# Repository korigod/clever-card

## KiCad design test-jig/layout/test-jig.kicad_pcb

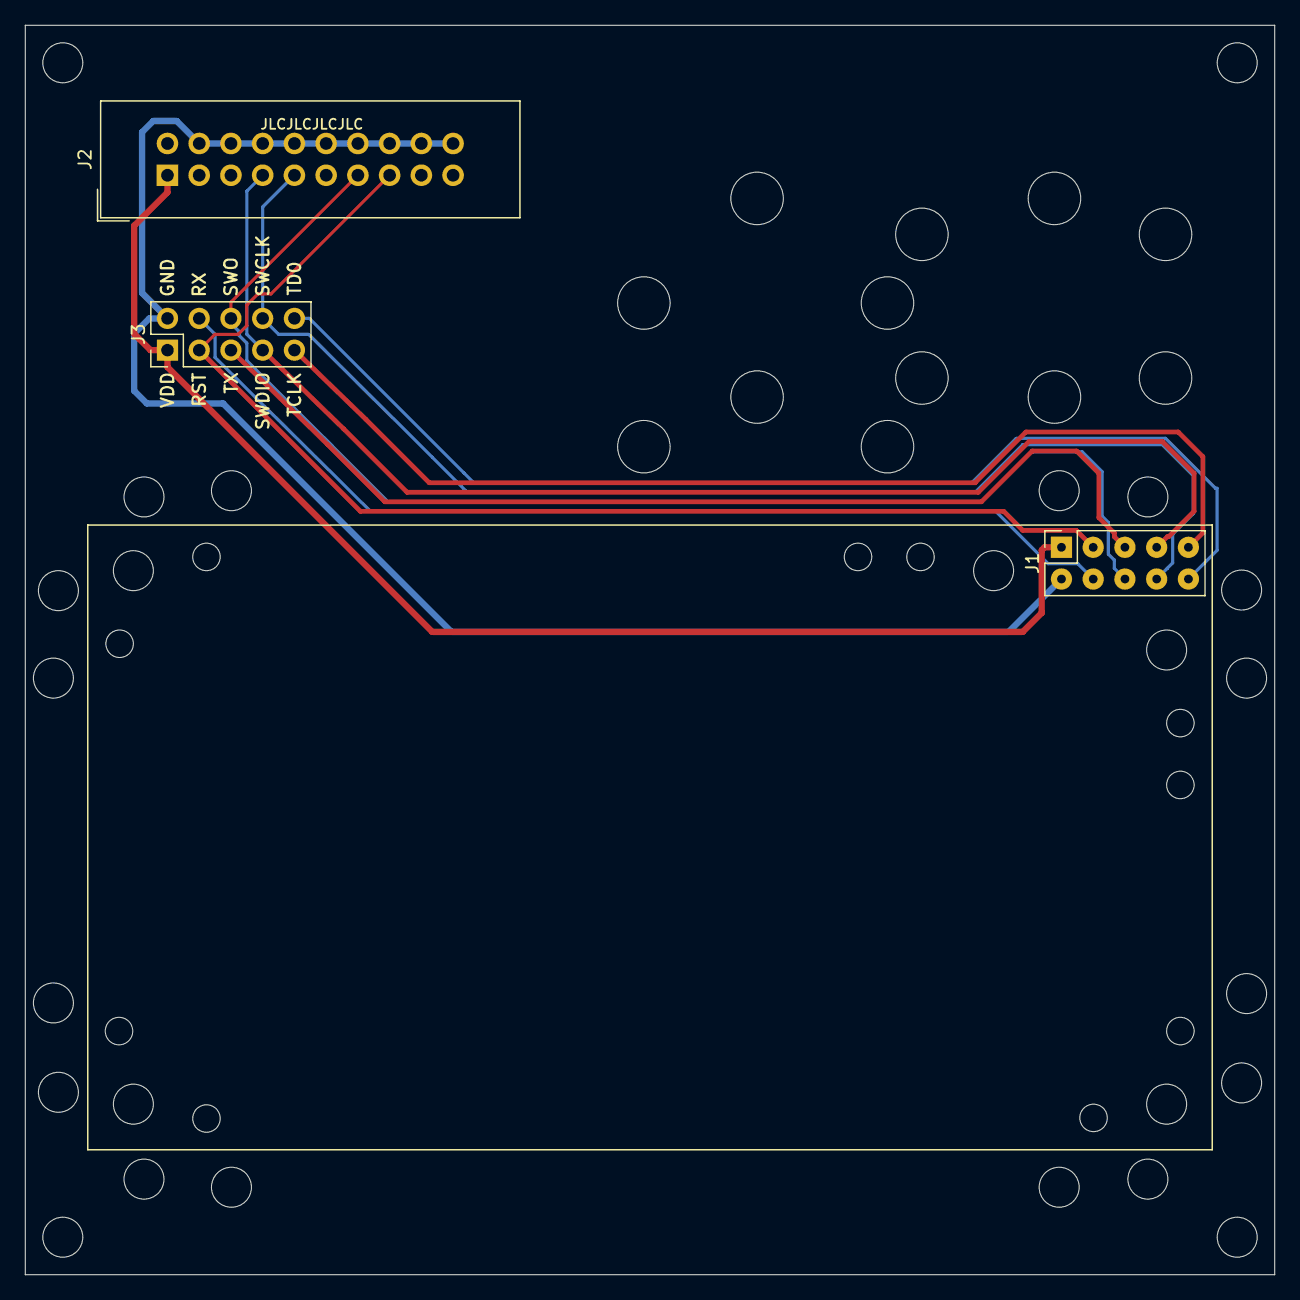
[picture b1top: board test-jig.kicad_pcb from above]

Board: 2 copper layers, 100.0 x 100.0 mm, 3 parts (0 on the bottom side), 10 nets.

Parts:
J1: Conn_02x05_Odd_Even; PinHeader_2x05_P2.54mm_D0.7mm_Vertical
J2: Conn_02x10_Odd_Even; IDC-Header_2x10_P2.54mm_Vertical
J3: Conn_02x05_Odd_Even; PinHeader_2x05_P2.54mm_Vertical

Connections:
DBG_SWCLK: J1.8, J2.9, J3.8
DBG_SWDIO: J1.7, J2.7, J3.7
DBG_SWO: J1.6, J2.13, J3.6
ETM_TCLK: J1.9, J3.9
ETM_TD0: J1.10, J3.10
GND: J1.2, J2.4, J2.6, J2.8, J2.10, J2.12, J2.14, J2.16, J2.18, J2.20, J3.2
RESET: J1.3, J2.15, J3.3
USART_RX: J1.4, J3.4
USART_TX: J1.5, J3.5
VDD: J1.1, J2.1, J3.1

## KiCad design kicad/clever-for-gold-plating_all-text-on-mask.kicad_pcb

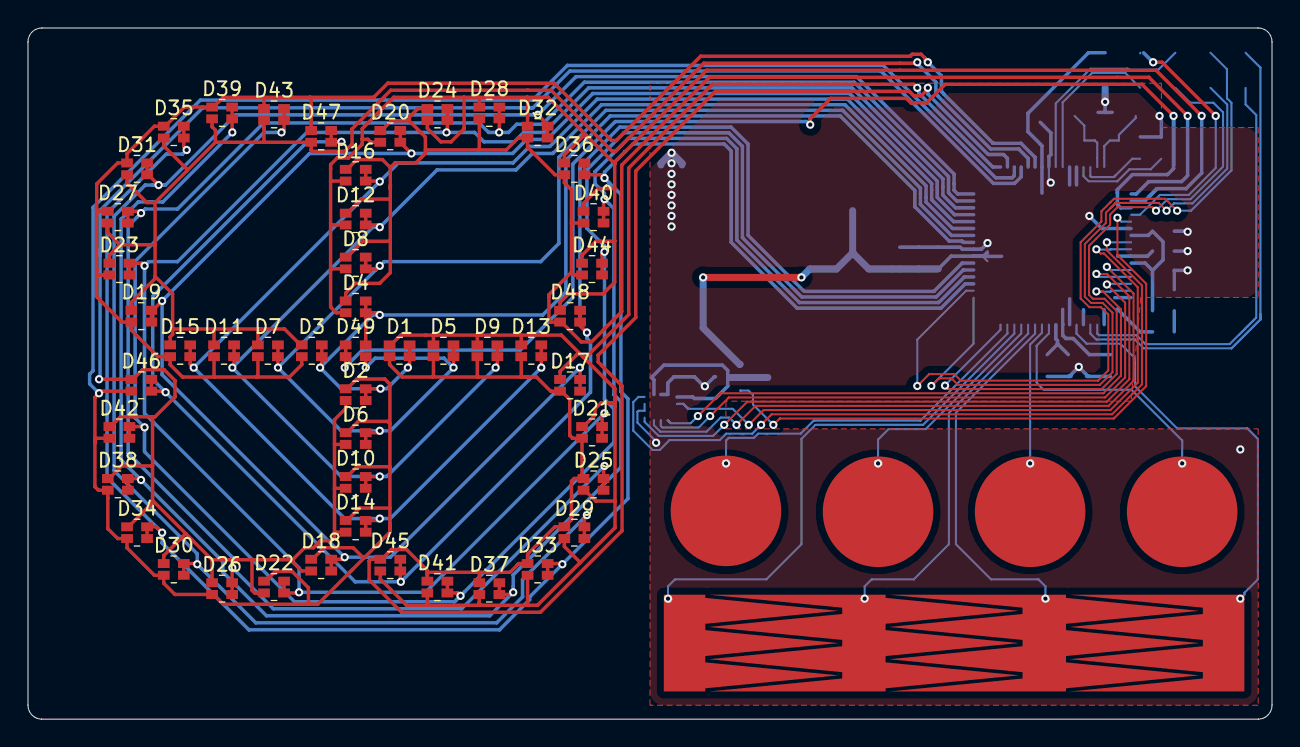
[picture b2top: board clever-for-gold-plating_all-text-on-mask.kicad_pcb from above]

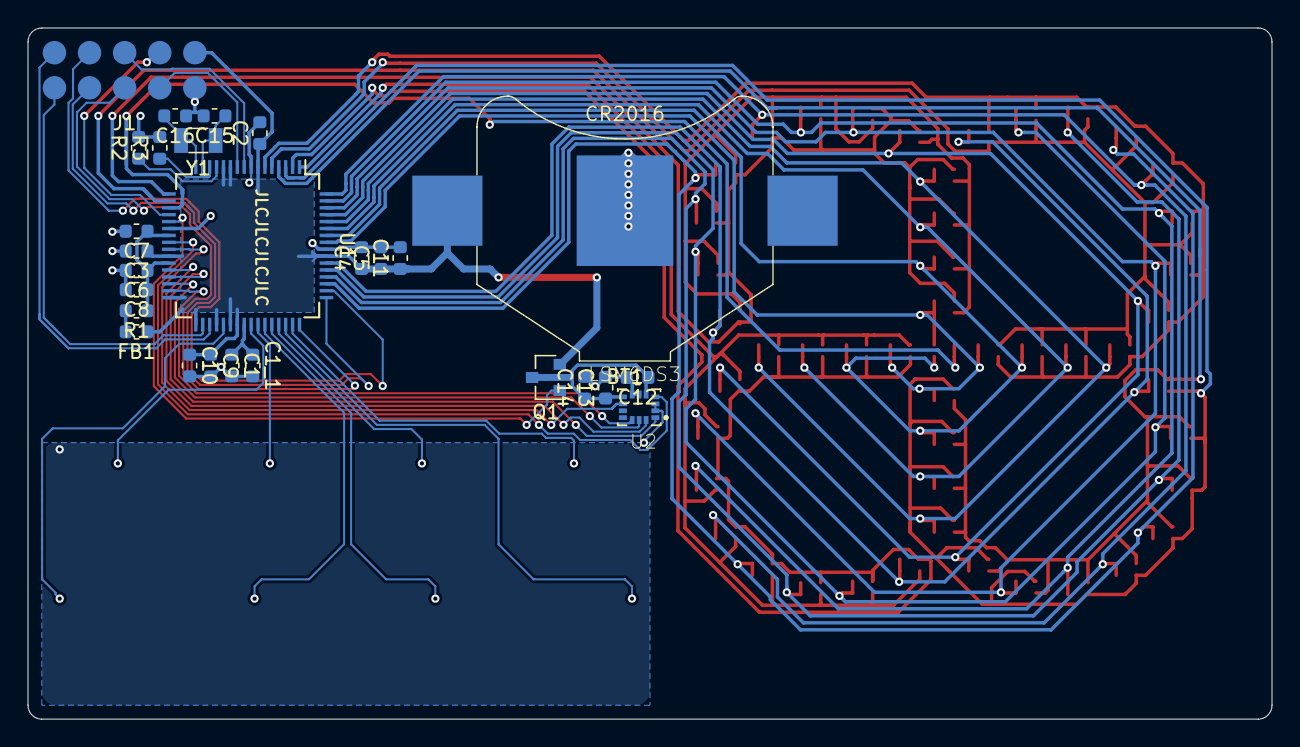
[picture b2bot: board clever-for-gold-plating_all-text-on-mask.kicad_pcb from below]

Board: 2 copper layers, 90.0 x 50.0 mm, 85 parts (27 on the bottom side), 54 nets.

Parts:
BT1: Battery_Cell; BatteryHolder_Keystone_3026_1x2016
C1, C5: 1uF; C_0603_1608Metric
C1_1, C8, C10, C14: 10uF; C_0603_1608Metric
C2, C3, C4, C9, C12, C13: 0.1uF; C_0603_1608Metric
C6, C7: 10nF; C_0603_1608Metric
C11: 47uF; C_0603_1608Metric
C15, C16: 22pF; C_0603_1608Metric
D1, D2, D3, D4, D5, D6, D7, D8, D9, D10, D11, D12, D13, D14, D15, D16, D17, D18, D19, D20, D21, D22, D23, D24, D25, D26, D27, D28, D29, D30, D31, D32, D33, D34, D35, D36, D37, D38, D39, D40, D41, D42, D43, D44, D45, D46, D47, D48, D49: LED_Dual_AACC; LED_DUAL_0606
FB1: Ferrite_Bead_Small; L_0603_1608Metric
J1: POGO_10PADS; TestPoints_2x05_P2.54_D1.7
Q1: Q_PMOS_GSD; SOT-23
R1: 1; R_0603_1608Metric
R2, R3: 0; R_0603_1608Metric
TS1, TS2, TS3, TS4: TOUCH_PAD; TouchPad_D8.0mm_Mask
TS5: TOUCH_SLIDER_4PADS; TouchSlider-4_42x7mm
U1: EFM32LG232F64; LQFP-64_10x10mm_P0.5mm
U2: LSM6DS3
Y1: 32768Hz; Crystal_SMD_3215-2Pin_3.2x1.5mm
svg2mod: G***; Text_Slide_Signika_Mask
svg2mod#2: G***; Text_Contacts_Reversed-2_Mask
svg2mod#3: G***; Text_Position_Mask
svg2mod#4: G***; Text_Name_9.5pt_Mask

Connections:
GND: BT1.2, C1.2, C1_1.2, C2.2, C3.2, C4.2, C5.2, C6.2, C7.2, C8.2, C9.2, C10.2, C11.2, C12.2, C13.2, C14.2, C15.2, C16.2, J1.2, R2.2, R3.2, U1.8, U1.22, U1.56, U2.2, U2.3, U2.6, U2.7
IMU_VDD: C12.1, C13.1, C14.1, Q1.3, U2.5, U2.8
LED_A0: D1.1, D5.1, D9.1, D13.1, D17.1, D21.1, D25.2, D29.2, D33.2, D37.2, D41.2, D45.2, U1.1
LED_A1: D1.2, D5.2, D9.2, D13.2, D17.2, D21.2, D25.1, D29.1, D33.1, D37.1, D41.1, D45.1, U1.2
LED_A2: D2.1, D6.1, D10.1, D14.1, D18.1, D22.1, D26.2, D30.2, D34.2, D38.2, D42.2, D46.2, U1.3
LED_A3: D2.2, D6.2, D10.2, D14.2, D18.2, D22.2, D26.1, D30.1, D34.1, D38.1, D42.1, D46.1, U1.4
LED_A4: D3.1, D7.1, D11.1, D15.1, D19.1, D23.1, D27.2, D31.2, D35.2, D39.2, D43.2, D47.2, U1.5
LED_A5: D3.2, D7.2, D11.2, D15.2, D19.2, D23.2, D27.1, D31.1, D35.1, D39.1, D43.1, D47.1, U1.6
LED_A6: D4.1, D8.1, D12.1, D16.1, D20.1, D24.1, D28.2, D32.2, D36.2, D40.2, D44.2, D48.2, U1.17
LED_A7: D4.2, D8.2, D12.2, D16.2, D20.2, D24.2, D28.1, D32.1, D36.1, D40.1, D44.1, D48.1, U1.18
LED_A8: D49.1, D49.2, U1.19
LED_K0: D1.3, D1.4, D2.3, D2.4, D3.3, D3.4, D4.3, D4.4, D49.3, U1.57
LED_K1: D5.3, D5.4, D6.3, D6.4, D7.3, D7.4, D8.3, D8.4, D49.4, U1.58
LED_K2: D9.3, D9.4, D10.3, D10.4, D11.3, D11.4, D12.3, D12.4, U1.59
LED_K3: D13.3, D13.4, D14.3, D14.4, D15.3, D15.4, D16.3, D16.4, U1.60
LED_K4: D17.3, D17.4, D18.3, D18.4, D19.3, D19.4, D20.3, D20.4, U1.61
LED_K5: D21.3, D21.4, D22.3, D22.4, D23.3, D23.4, D24.3, D24.4, U1.62
LED_K6: D25.3, D25.4, D26.3, D26.4, D27.3, D27.4, D28.3, D28.4, U1.63
LED_K7: D29.3, D29.4, D30.3, D30.4, D31.3, D31.4, D32.3, D32.4, U1.64
LED_K8: D33.3, D33.4, D34.3, D34.4, D35.3, D35.4, D36.3, D36.4, U1.51
LED_K9: D37.3, D37.4, D38.3, D38.4, D39.3, D39.4, D40.3, D40.4, U1.52
LED_K10: D41.3, D41.4, D42.3, D42.4, D43.3, D43.4, D44.3, D44.4, U1.53
LED_K11: D45.3, D45.4, D46.3, D46.4, D47.3, D47.4, D48.3, D48.4, U1.54
LFXTAL_N: C16.1, U1.16, Y1.2
LFXTAL_P: C15.1, U1.15, Y1.1
MCU_AVDD: C6.1, C7.1, C8.1, R1.2, U1.23, U1.27
unnamed: C1.1, C1_1.1, U1.40
unnamed: FB1.2, R1.1
unnamed: J1.3, U1.20
unnamed: J1.4, U1.10
unnamed: J1.5, U1.9
unnamed: J1.6, U1.48
unnamed: J1.7, U1.50
unnamed: J1.8, U1.49
unnamed: J1.9, U1.35
unnamed: J1.10, U1.34
unnamed: Q1.1, U1.21
unnamed: U1.29, U2.1
unnamed: U1.28, U2.14
unnamed: U1.30, U2.13
unnamed: U1.31, U2.12
unnamed: U1.24, U2.4
unnamed: U1.25, U2.9
unnamed: TS5.1, U1.46
unnamed: TS5.2, U1.44
unnamed: TS5.3, U1.43
unnamed: TS5.4, U1.37
unnamed: R2.1, U1.13
unnamed: R3.1, U1.14
TOUCH_PAD0: TS1.1, U1.47
TOUCH_PAD1: TS2.1, U1.45
TOUCH_PAD2: TS3.1, U1.42
TOUCH_PAD3: TS4.1, U1.41
VDD: BT1.1, C2.1, C3.1, C4.1, C5.1, C9.1, C10.1, C11.1, FB1.1, J1.1, Q1.2, U1.7, U1.11, U1.12, U1.26, U1.32, U1.33, U1.36, U1.38, U1.39, U1.55

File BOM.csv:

"Id";"Designator";"Package";"Quantity";"Designation";"Model";"Price";"Supplier and ref";
1;"C11";"C_0603_1608Metric";1;"47uF";"Murata GRM188R60J476ME15D";0.097;"https://lcsc.com/product-detail/Multilayer-Ceramic-Capacitor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";
2;"D1,D2,D3,D4,D5,D6,D7,D8,D9,D10,D11,D12,D13,D14,D15,D16,D17,D18,D19,D20,D21,D22,D23,D24,D25,D26,D27,D28,D29,D30,D31,D32,D33,D34,D35,D36,D37,D38,D39,D40,D41,D42,D43,D44,D45,D46,D47,D48,D49";"LED_DUAL_0606";49;"LED_Dual_AACC";"Lite-On LTST-C195KGJRKT";0.0367;"https://lcsc.com/product-detail/Light-Emitting-Diodes-LED_SM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";
3;"R1";"R_0603_1608Metric";1;"1";"Walsin WR06W1R00FTL";0.0017;"https://lcsc.com/product-detail/Chip-Resistor-Surface-Mount_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";
4;"U1";"LQFP-64_10x10mm_P0.5mm";1;"EFM32LG232F64";"SiLabs EFM32LG232F64";2.5;;
5;"Y1";"Crystal_SMD_3215-2Pin_3.2x1.5mm";1;"32768Hz";"Yangxing X321532768KGB2SI";0.1575;"https://lcsc.com/product-detail/SMD-Crystals_Yangxing-Tech-Y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";
6;"C1,C5";"C_0603_1608Metric";2;"1uF";"Samsung CL10A105KB8NNNC";0.0083;"https://lcsc.com/product-detail/Multilayer-Ceramic-Capacitor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";
7;"C3,C4,C9,C12,C13,C2";"C_0603_1608Metric";6;"0.1uF";"Samsung CL10B104KB8NNNC";0.0067;"https://lcsc.com/product-detail/Multilayer-Ceramic-Capacitor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";
8;"C6,C7";"C_0603_1608Metric";2;"10nF";"Samsung CL10B103JB8NNNC";0.0071;"https://lcsc.com/product-detail/Multilayer-Ceramic-Capacitor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";
9;"C1_1,C8,C10,C14";"C_0603_1608Metric";4;"10uF";"Samsung CL10A106KP8NNNC";0.0260;"https://lcsc.com/product-detail/Multilayer-Ceramic-Capacitor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";
10;"R2,R3";"R_0603_1608Metric";2;"0";"Walsin WR06X0000PTL";0.0017;"https://lcsc.com/product-detail/Chip-Resistor-Surface-Mount_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";
11;"U2";"LSM6DS3";1;"LSM6DS3";"STM LSM6DS3TR";1.0261;"https://lcsc.com/product-detail/Others_STMicroelectronics_LS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";
12;"BT1";"BatteryHolder_Keystone_3026_1x2016";1;"Battery_Cell";"Keystone 3026";0.5227;"https://ru.mouser.com/ProductDetail/Keystone-Electronics/3026";
13;"C15,C16";"C_0603_1608Metric";2;"22pF";"Walsin 0603N220F101CT";0.0111;"https://lcsc.com/product-detail/Others_Huaxin-S-T-0603N220F1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";
14;"Q1";"SOT-23";1;"Q_PMOS_GSD";"Nexperia BSH203";0.1273;"https://lcsc.com/product-detail/MOSFET_Nexperia_BSH203-215_N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";
15;"FB1";"L_0603_1608Metric";1;"Ferrite_Bead_Small";"Murata BLM18HE102SN1D / TDK MMZ1608R102ATA00";0.0377;"https://lcsc.com/product-detail/Ferrite-Beads-And-Chips_muRa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";
16;;"CR2016";1;"";"Panasonic CR2016";0.21;"https://aliexpress.com/item/Panasonic-Top-Quality-Lithium-Ba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";

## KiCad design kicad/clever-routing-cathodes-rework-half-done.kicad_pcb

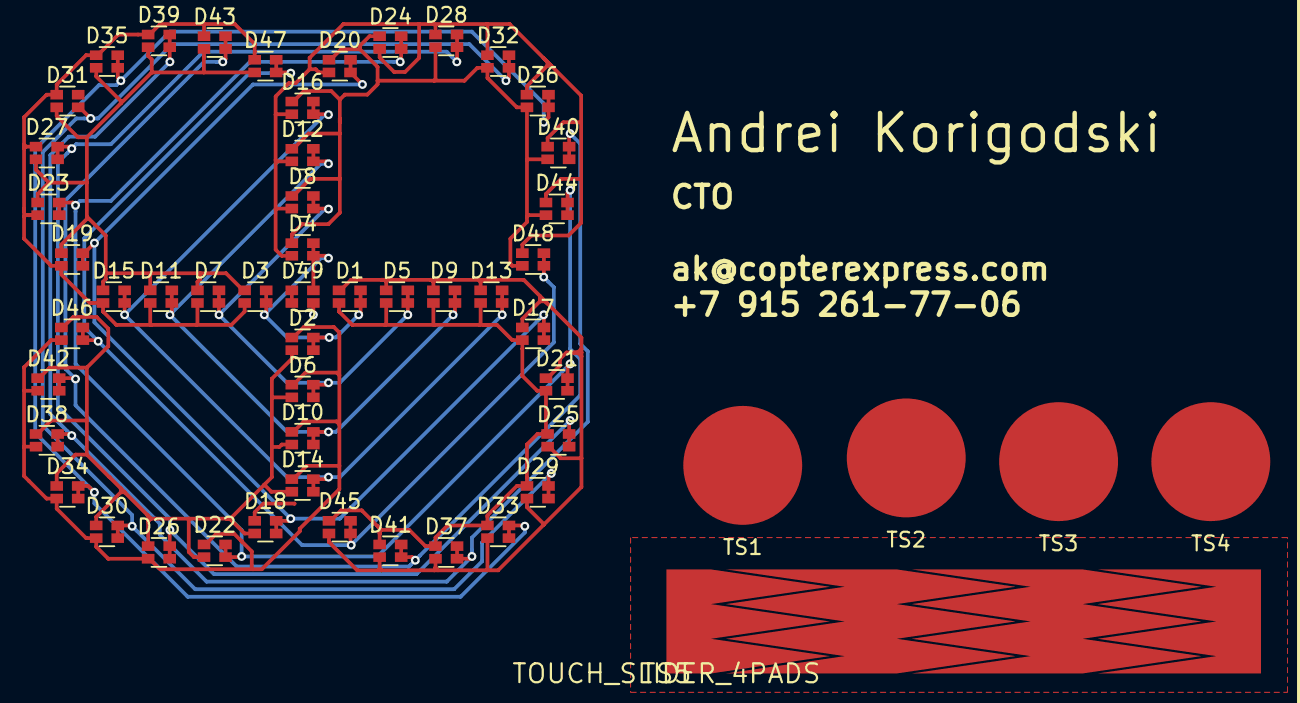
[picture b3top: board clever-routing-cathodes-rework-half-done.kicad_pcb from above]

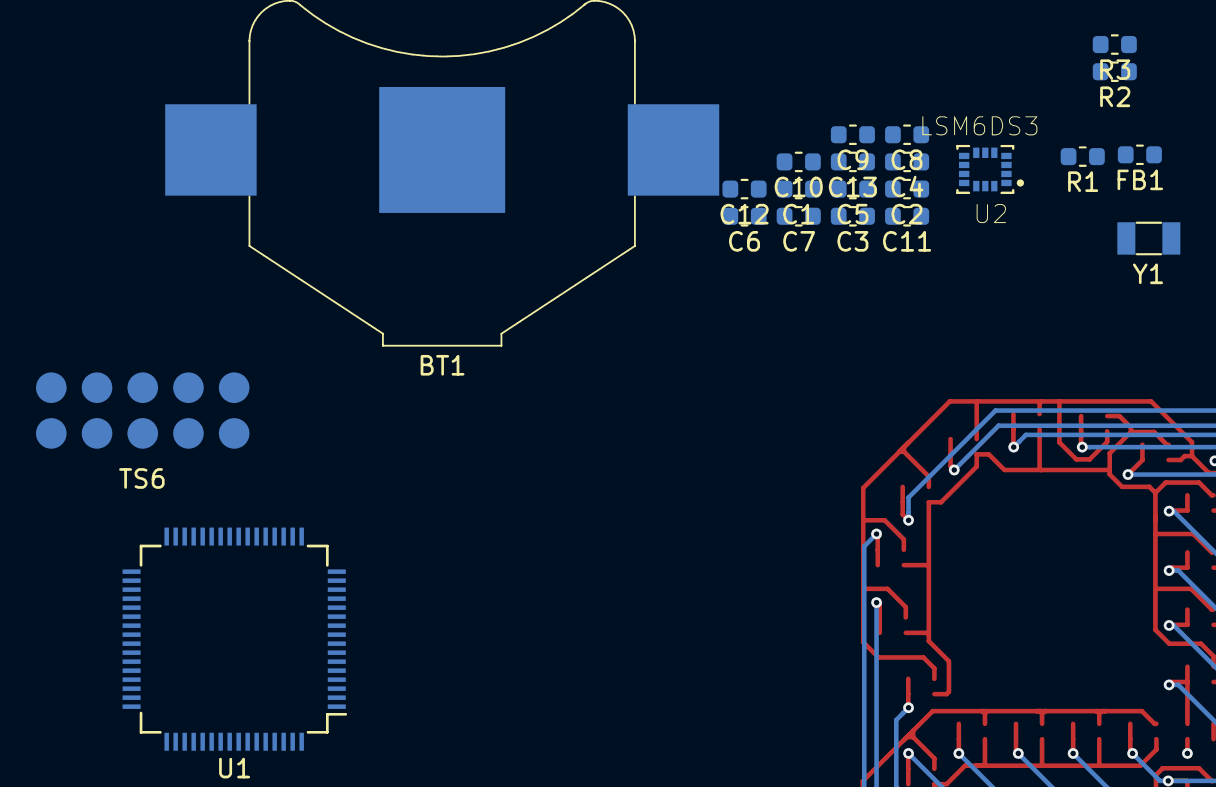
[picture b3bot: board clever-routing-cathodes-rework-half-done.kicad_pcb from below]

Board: 2 copper layers, 76 parts (22 on the bottom side), 52 nets.

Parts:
BT1: Battery_Cell; BatteryHolder_Keystone_3026_1x2016
C1: 1uF; C_0603_1608Metric
C2, C3, C4, C9, C12, C13: 0.1uF; C_0603_1608Metric
C5, C8: 10uF; C_0603_1608Metric
C6, C7: 10nF; C_0603_1608Metric
C10: 3.3uF; C_0603_1608Metric
C11: 100uF; C_0603_1608Metric
D1, D2, D3, D4, D5, D6, D7, D8, D9, D10, D11, D12, D13, D14, D15, D16, D17, D18, D19, D20, D21, D22, D23, D24, D25, D26, D27, D28, D29, D30, D31, D32, D33, D34, D35, D36, D37, D38, D39, D40, D41, D42, D43, D44, D45, D46, D47, D48, D49: LED_Dual_AACC; LED_DUAL_0606
FB1: Ferrite_Bead_Small; L_0603_1608Metric
R1: 1; R_0603_1608Metric
R2, R3: 0; R_0603_1608Metric
TS1, TS2, TS3, TS4: TOUCH_PAD; TouchPad_D8.0mm
TS5: TOUCH_SLIDER_4PADS; TouchSlider-4_40x7mm
TS6: POGO_10PADS; TestPoints_2x05_P2.54_D1.7
U1: EFM32LG232F64; LQFP-64_10x10mm_P0.5mm
U2: LSM6DS3
Y1: 32768Hz; Crystal_SMD_3215-2Pin_3.2x1.5mm

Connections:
GND: BT1.2, C1.2, C2.2, C3.2, C4.2, C5.2, C6.2, C7.2, C8.2, C9.2, C10.2, C11.2, C12.2, C13.2, R2.2, R3.2, TS6.2, U1.8, U1.11, U1.12, U1.21, U1.22, U1.32, U1.33, U1.36, U1.38, U1.56, U2.2, U2.3, U2.6, U2.7
LED_A0: D1.1, D5.1, D9.1, D13.1, D17.1, D21.1, D25.2, D29.2, D33.2, D37.2, D41.2, D45.2, U1.1
LED_A1: D1.2, D5.2, D9.2, D13.2, D17.2, D21.2, D25.1, D29.1, D33.1, D37.1, D41.1, D45.1, U1.2
LED_A2: D2.1, D6.1, D10.1, D14.1, D18.1, D22.1, D26.2, D30.2, D34.2, D38.2, D42.2, D46.2, U1.3
LED_A3: D2.2, D6.2, D10.2, D14.2, D18.2, D22.2, D26.1, D30.1, D34.1, D38.1, D42.1, D46.1, U1.4
LED_A4: D3.1, D7.1, D11.1, D15.1, D19.1, D23.1, D27.2, D31.2, D35.2, D39.2, D43.2, D47.2, U1.5
LED_A5: D3.2, D7.2, D11.2, D15.2, D19.2, D23.2, D27.1, D31.1, D35.1, D39.1, D43.1, D47.1, U1.6
LED_A6: D4.1, D8.1, D12.1, D16.1, D20.1, D24.1, D28.2, D32.2, D36.2, D40.2, D44.2, D48.2, U1.17
LED_A7: D4.2, D8.2, D12.2, D16.2, D20.2, D24.2, D28.1, D32.1, D36.1, D40.1, D44.1, D48.1, U1.18
LED_A8: D49.1, D49.2, U1.19
LED_K0: D1.3, D1.4, D2.3, D2.4, D3.3, D3.4, D4.3, D4.4, D49.3, U1.51
LED_K1: D5.3, D5.4, D6.3, D6.4, D7.3, D7.4, D8.3, D8.4, D49.4, U1.52
LED_K2: D9.3, D9.4, D10.3, D10.4, D11.3, D11.4, D12.3, D12.4, U1.53
LED_K3: D13.3, D13.4, D14.3, D14.4, D15.3, D15.4, D16.3, D16.4, U1.54
LED_K4: D17.3, D17.4, D18.3, D18.4, D19.3, D19.4, D20.3, D20.4, U1.57
LED_K5: D21.3, D21.4, D22.3, D22.4, D23.3, D23.4, D24.3, D24.4, U1.58
LED_K6: D25.3, D25.4, D26.3, D26.4, D27.3, D27.4, D28.3, D28.4, U1.59
LED_K7: D29.3, D29.4, D30.3, D30.4, D31.3, D31.4, D32.3, D32.4, U1.60
LED_K8: D33.3, D33.4, D34.3, D34.4, D35.3, D35.4, D36.3, D36.4, U1.61
LED_K9: D37.3, D37.4, D38.3, D38.4, D39.3, D39.4, D40.3, D40.4, U1.62
LED_K10: D41.3, D41.4, D42.3, D42.4, D43.3, D43.4, D44.3, D44.4, U1.63
LED_K11: D45.3, D45.4, D46.3, D46.4, D47.3, D47.4, D48.3, D48.4, U1.64
MCU_AVDD: C6.1, C7.1, C8.1, R1.2, U1.23, U1.27
unnamed: C1.1, U1.40
unnamed: FB1.2, R1.1
unnamed: TS6.3, U1.20
unnamed: TS6.4, U1.10
unnamed: TS6.5, U1.9
unnamed: TS6.6, U1.48
unnamed: TS6.7, U1.50
unnamed: TS6.8, U1.49
unnamed: TS6.9, U1.35
unnamed: TS6.10, U1.34
unnamed: U1.15, Y1.1
unnamed: U1.16, Y1.2
unnamed: U1.29, U2.1
unnamed: U1.28, U2.14
unnamed: U1.30, U2.13
unnamed: U1.31, U2.12
unnamed: U1.24, U2.4
unnamed: U1.25, U2.9
unnamed: TS5.1, U1.44
unnamed: TS5.2, U1.45
unnamed: TS5.3, U1.46
unnamed: TS5.4, U1.47
unnamed: R2.1, U1.13
unnamed: R3.1, U1.14
TOUCH_PAD0: TS1.1, U1.37
TOUCH_PAD1: TS2.1, U1.41
TOUCH_PAD2: TS3.1, U1.42
TOUCH_PAD3: TS4.1, U1.43
VDD: BT1.1, C2.1, C3.1, C4.1, C5.1, C9.1, C10.1, C11.1, C12.1, C13.1, FB1.1, TS6.1, U1.7, U1.26, U1.39, U1.55, U2.5, U2.8

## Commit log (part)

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2019-03-18 components: initial revision
2019-03-18 schematics: initial revision
2019-03-18 led_pattern_gen: initial revision
2019-03-22 components: add EFM32LG232F64
    It was generated from .csv file with csv2kicad tool.
2019-03-22 schematics: update card
2019-03-22 footprints: add red-green dual LED
2019-03-22 schematics: decouple MCU and use red-green LEDs
2019-03-23 schematics: connect power to MCU
2019-03-24 schematics: check if specified LED count achieved
2019-03-24 schematics: add capacitive touch pads
2019-03-24 requirements: initial revision
2019-03-24 pins: add file with pin assignments
2019-03-24 schematics: add 32768 Hz crystal
2019-03-24 schematics: add SPI and INT lines between MCU and IMU
2019-03-24 pins: update pin assignment to add one more LED line
2019-03-24 schematics: use ERC (electrical rule check)
2019-03-25 schematics: suppress "Insufficient drive" ERC warning
2019-03-25 schematics: specify the crystal footprint
2019-03-25 schematics: add debug and programming interface
2019-03-25 schematics: specify correct footprint for battery holder
    It's fully compatible with Keystone 3028.
2019-03-25 gitignore: add python temporary files and vscode settings
2019-03-26 footprints: add LSM6DS3
2019-03-28 footprints: add touch slider generated by wizard
2019-03-28 gitignore: add kicad autosave files
2019-03-28 schematics: fix LED footprint name
2019-03-29 schematics: connect unused EFM32 pins to circuit common
2019-03-29 footprints: add capacitive touch pad
2019-03-30 footprints: add debug/programming pads for spring loaded connector
2019-03-31 led_pattern: move matplotlib plotting and GUI to separate module
2019-04-01 led_pattern: improve readability
2019-04-01 led_pattern: fix calculations in case linear_radius != 1
2019-04-01 led_pattern: swap linear leds to make layout easier
2019-04-03 footprints: add new generated footprint for CR2016 holder
2019-04-03 schematics: modify LED connection
2019-04-03 led_pattern: fix LED arcs generation
2019-04-03 led_pattern: add pcbnew script for automated layout
2019-04-03 schematics: add larger IMU decoupling capacitor
2019-04-03 schematics: swap LED pins to simplify layout
2019-04-04 schematics: simplify MCU analog power decoupling
2019-04-06 schematics: assign names to crystal nets
    It enables KiCad differential pair length matching tools.
2019-04-06 schematics: pass ground net for unused IMU pins as arg
2019-04-06 schematics: swap touch sense pins to make layout simpler
2019-04-06 schematics: add P-MOSFET to cut IMU power
    It consumes several uA even when disabled.
2019-04-07 schematics: decouple MCU_AVDD better
    This reverts commit 16f4ae7.
2019-04-08 led_pattern: make compatible with python 2
    KiCad uses python 2.7.
2019-04-09 schematics: specify debug pads ref_prefix
2019-04-09 footprints: update battery holder footprint
2019-04-09 footprints: update LED footprint
2019-04-10 footprints: add touch button with circle in mask layer
2019-04-13 kicad: first manufactured revision
2019-04-14 BOM: first revision
2019-04-16 components: remove unused RGB led
2019-07-02 Commit ALL the files
2019-07-06 firmware-experimantal: use DMA for SPI transfer
2019-07-07 firmware-experimental: migrate to VS Code from Simplicity Studio
2019-07-07 pins: clarify the assignment
    IMU_FET is the gate of the N-MOSFET which cuts LSM6DS3's power
    when it's not in use to minimize power consumption.
2019-07-08 firmware-experimental: add minimal FreeRTOS v10 example
2019-07-08 firmware: first revision based on FreeRTOS
2019-07-08 firmware: remove LED-control test code
2019-07-08 firmware: remove unnecessary debug statements
2019-07-08 firmware: use GPIO interrupt to initiate IMU query
2019-07-08 firmware: rename initDma functions to better reflect their purpose
2019-07-08 firmware: use INT1 pin of LSM6DS3 for Data Ready IRQ
2019-07-09 firmware: use task notification to trigger IMU query
    The problem with direct triggering from ISR is that all the tasks can
    be starved of processing time if the data is being transfered all the
    time — e.g. when IMU update rate is very high or when the debugger is
    used to pause the execution (the IMU itself is not being paused and
    it looks for the firmware like IMU is constantly triggering DRDY line
    even although the last measurement is not processed yet).
2019-07-09 firmware: use ridiculously small stack size for tasks
    Just to check how small it can be. We have stack overflow hook anyway.
2019-07-09 firmware: use \n for newline instead of \r\n
2019-07-09 firmware: remove unnecessary constant
    It's defined in <limits.h> anyway.
2019-07-09 firmware: use hardware timer to implement µs delay
2019-07-09 firmware: fix SPI communication on low baudrates
    It looks like if we send commands without delay on low baudrate
    (100kbps or less), the hardware CS control does not deassert the line
    so the transmission is corrupted and the LSM6DS3 does not start.
2019-07-09 firmware: move writing to IMU registers to separate function
2019-07-09 firmware: rewrite timer module
    Now it provides absolute time with microsecond granularity
    instead of just blocking delays.
2019-07-09 firmware: throttle IMU queries a bit
2019-07-09 firmware: add task to debug the release build
2019-07-10 firmware: edit unclear comment
2019-07-10 firmware: convert names to camelCase
    To be consistent with FreeRTOS API and emlib. Also the names of the
    statically allocated buffers for tasks and queues are updated to
    better reflect their meaning and to get rid of trailing underscores.
2019-07-11 firmware: toggle leds inside the ISR
    This way the context switching delays are minimized. Minimal control
    cycle time for a single LED is now just 8 μs, and the minimal LED on
    time is decreased to 3 μs.
    The downside is the increase of the interrupt latency. However, now
    there are no more such time-sensitive tasks and if they appear, the
    priority of the timer interrupt can be decreased. This, of course,
2019-07-11 firmware: fix whitespace
2019-07-11 firmware: remove the unused variable
2019-07-13 firmware: use separate list of LED IDs
2019-07-13 firmware: increase max length of the task name
2019-07-16 firmware: add fake_function_framework
2019-07-16 [WIP] firmware: add a few tests (not compiling yet)
2019-07-18 firmware-experimental: move first version of firmware there
2019-08-05 firmware: create empty project with ceedling & fff
2019-08-06 firmware: move board-specific values to separate header file
2019-08-06 firmware: use suiting assert for memory compare
2019-08-06 firmware: specify LED cathodes
2019-08-06 firmware: add functions to switch LED anodes
2019-08-06 firmware: add function to disable LEDs
2019-08-06 firmware: don't compare signed integer with unsigned one
2019-08-07 firmware: rename leds module to led_driver
2019-08-07 firmware: move LED pin structs to new module
2019-08-07 firmware: remove unnecessary function declaration
2019-08-07 firmware: fix an include
2019-08-08 firmware: add array of LED cathodes and anodes
2019-08-08 firmware: add array of LED output values
2019-08-10 firmware: add helper function to check cathodes equality
2019-08-10 firmware: rename LedWires to LedPins
2019-08-10 firmware: add function to switch on next LED
2019-08-10 firmware: fix initialization of LED pins array
2019-08-11 firmware: add functions to check for structs equality
2019-08-11 firmware: rename initLeds to initializeLedDriver
2019-08-12 firmware: fix style
2020-01-27 firmware: change target to EFM32TG232
2020-01-27 firmware: make led driver more robust
    Now only one anode pin is active at a time. It prevents short curcuit
    if two anode lines are connected by dirt or moisture — anode pads are
    close to each other at every LED.
2020-01-27 firmware: latch LED outputs every LED update loop
2020-01-28 firmware-experimental: add SWO printf example
2020-01-29 test-jig: first revision of the layout
2020-01-29 test-jig: route the traces
2020-01-29 test-jig: create gerbers for pcb production
2020-01-29 schematics: fix
2020-01-29 firmware: add ceedling config to run tests on target
    Now tests can be executed on the MCU with "ceedling project:target".
2020-01-29 firmware: move ceedling plugins to a separate dir
    To allow to pull ceedling from github to vendor dir.
2020-01-30 firmware: use #define to set constant
2020-01-30 firmware: add gamma=2 to led brightness control
2020-01-30 firmware: add timer module and manage leds with it
2020-01-30 firmware: make ledOutputs array public
    It's ok to change them and leave in inconsistent state because they are
    being latched anyway. Unfortunately, because we declare this array now
    without defining its length, vscode doesn't show array content in
    debugger. It can be fixed by including board.h, but it requires to move
    declaration of led structs to a new file to prevent circular dependency
    between board.h and led.h.
2020-01-30 firmware: add function to clear ledOutputs buffer
2020-01-30 firmware: add FreeRTOS task to control leds
2020-01-30 firmware: traverse nicely through all the leds
2020-01-30 firmware: add utterly cool led effects
2020-02-01 firmware: define min and max functions in common.h
2020-02-01 firmware: explicitly set stack_dummy size in makefile
    0x0400 is the default value, but it can be changed in future to free
    more RAM. The main stack won't contain much because almost everything
    is in tasks' stacks, and they are in .bss section.
2020-02-01 firmware: use consistent types
2020-02-01 firmware: add additionalSuiteSetUp weak declaration
    Now it's possible to define additionalSuiteSetUp function in test file
    and it will be called after default suiteSetUp, defined in yaml config.
2020-02-02 firmware: improve short circuit test
2020-02-02 firmware: report all short circuits instead of the first one
    Parameterized tests are supported quite poorly in Unity/Ceedling.
    Alternatives may include:
    - generating test .c file by custom script;
    - generating runner by custom script instead of ceedling.
2020-02-02 firmware: calculate test execution time
2020-02-03 firmware: run tests with release build options (-O3)
2020-02-03 firmware: configure assertions
2020-02-04 firmware: refine timer's minimal interval
2020-02-04 firmware: check timer's actual min delay duration
2020-02-04 firmware: fix led update issues
2020-08-09 firmware: reduce stack size
    We are running out of RAM on EFM32TG232F32 and we don't need large
    stack because all the large functions are in tasks which have
    stacks pre-allocated.
2020-08-09 firmware: analyze stack usage of release builds
2020-08-14 firmware: add vscode build&debug settings for EFM32LG
2020-08-18 firmware: fix EFM32LG232 SVD definition
    CHENS registers are read-write, not write-only.
2020-08-18 firmware: change test target to EFM32LG
    It's possible to create separate ceedling yamls for TG and LG MCUs but I'm not sure
    I'll ever use TG232 so for the time being let's just replace TG with LG here.
2020-08-18 firmware: execute CHIP_Init() before tests
2020-08-18 firmware: fix "FreeRTOS.h must be included before list.h" error
2020-08-18 firmware: make test exec time measurement FreeRTOS-compatible
    Now milliseconds value increments in SysTick handler if it's not
    provided by FreeRTOS or in FreeRTOS tick hook otherwise.
2020-08-18 firmware: fix make output formatting
2020-08-18 firmware: move SVD definitions out of sight
2020-08-18 firmware: add LSM6DS3 driver to Makefile
2020-08-18 firmware: don't compile FreeRTOS for tests
    Ceedling compiles FreeRTOS if it's in source paths and then we get multiple
    definition error when we are trying to mock FreeRTOS functions.
    Another workaround may be to use fff plugin (#include "mock_queue.h"...) but
    I'm not sure it will work because other header files are including queue.h.
2020-08-18 firmware: add default suiteTearDown for testing on target
    This serves two purposes: we can use leds to check if test passes and
    we circumvent a problem with suiteTearDown — for some weird reason
    when all the tests in directory are run using test:path directive,
    suiteTearDown is being included in the test runner even if it's
    absent in the file.
2020-08-18 firmware: add tests for IMU RTOS task
